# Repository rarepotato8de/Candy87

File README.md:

# Candy87: A universal TKL PCB 💙
The Candy87 Hotswap PCB was exclusively made for and in cooperation with [Candykeys](https://candykeys.com/) and designed to fit the Geonworks F1-8X V2 and other TKL keyboards. It supports many layout options and has awesome features!

## Features
- H87/H88 Compatible
- ISO and/or ANSI Support (See supported layout notes!)
- Standard and Tsangan Bottom Row
- O-Ring Cutouts
- Breakable USB-C Port (Daughterboard can be used with JST)
- Indicator LED's for Caps- and Scrolllock
- RP2040 Chip
- Broken-out GPIO Pins
- QMK/VIAL Support

## Firmware & Flashing
[QMK](https://github.com/qmk/qmk_firmware/tree/master/keyboards/candykeys/candy87) and [VIAL](https://github.com/vial-kb/vial-qmk/tree/vial/keyboards/candykeys/candy87) firmwares are available in their repositories. The compiled VIAL firmware can be found [here](https://github.com/rarepotato8de/Candy87/blob/main/firmware/Candy87_DEFAULT.uf2).

To flash the PCB the first time, you just have to plug it into your computer via. USB-C or Daughterboard and then in your explorer there should appear a new drive medium called "RPI-RP2" or similar. Just drag&drop the .UF2 file onto the drive and the window should automatically close and the PCB will now be flashed and functional.
For flashing it another time, plug in the PCB and hold down the "BOOT" button on the backside of the PCB, press the "RESET" button two times and then release the "BOOT" button again. After that the "RPI-RP2" medium should appear.

## Supported layouts

> [!IMPORTANT]
> Due to hotswap sockets interfering with both ANSI and ISO support, only one of these options can be used at a time.
> Candykeys version comes with ISO by default, but by resoldering two hotswap sockets it can be ANSI. See picture below (it's resoldered to ANSI)

## Breakable USB-C Port
> [!CAUTION]
> Be careful when removing/ breaking-off the USB-C port. It should be done with caution and pliers.
> It's recommended to place the PCB on a flat surface (e.g. a table), with the USB-C port "hanging" off the side and then wiggling up and down with your pliers until it breaks off.

> [!CAUTION]
> Please do this step outside or somewhere but inside.
> You should wear glasses and a mask to prevent any health risks from the FR4 dust.

https://github.com/user-attachments/assets/5fa9985e-4570-457c-9966-bd2f55c6e134

## Open Source

Candy87 was only possible thanks to other open-source projects and libraries (see [Credits](#credits)), so it's open source as well!
You can even order the PCB yourself with the provided files for JLCPCB, and it's pretty affordable :)

## Credits

This project would not exist without these open-source libraries and projects. Massive thanks to all of them!

| Library | Author | Source |
|---|---|---|
| marbastlib | ebastler & contributors | [github.com/ebastler/marbastlib](https://github.com/ebastler/marbastlib) |
| MX_Alps_Hybrid, MX_Only | ai03 | [github.com/ai03-2725/MX_Alps_Hybrid](https://github.com/ai03-2725/MX_Alps_Hybrid) |
| random-keyboard-parts | ai03 | [github.com/ai03-2725/random-keyboard-parts.pretty](https://github.com/ai03-2725/random-keyboard-parts.pretty) |
| bakeneko-60-pcb-rescue | kkatano | [github.com/kkatano/bakeneko-60](https://github.com/kkatano/bakeneko-60) |
| RP2040 libraries | Raspberry Pi Ltd | [datasheets.raspberrypi.com](https://datasheets.raspberrypi.com/) |

License texts can be found in [`hardware/libs/licenses/`](hardware/libs/licenses/).

## Start of this project
The project came up in the beginning of 2024 when Geonworks announced another groupbuy for his popular keyboard, the F1-8X V2. For european fellas, Candykeys wanted to offer an ISO hotswap PCB. So we talked, made plans and finally built this awesome project together!
There was a lot demand for it, people were interested and excited for it and me too! So I'm super honored to be part of this and will look forward for further projects. The Candy87 is the first project I've ever done in cooperation with a company, so I gave my best at all time. Even though we have had an issue with our first prototype, because of switch interference, the second version not only fixed this issue, but was improved even more. From the beginning it was made to be open source, because both Candykeys and I are a fan of this concept.

Big shoutout and thanks to @zitres 🍋🍋 and @candykeys 💙

## Questions?
Feel free to message me!

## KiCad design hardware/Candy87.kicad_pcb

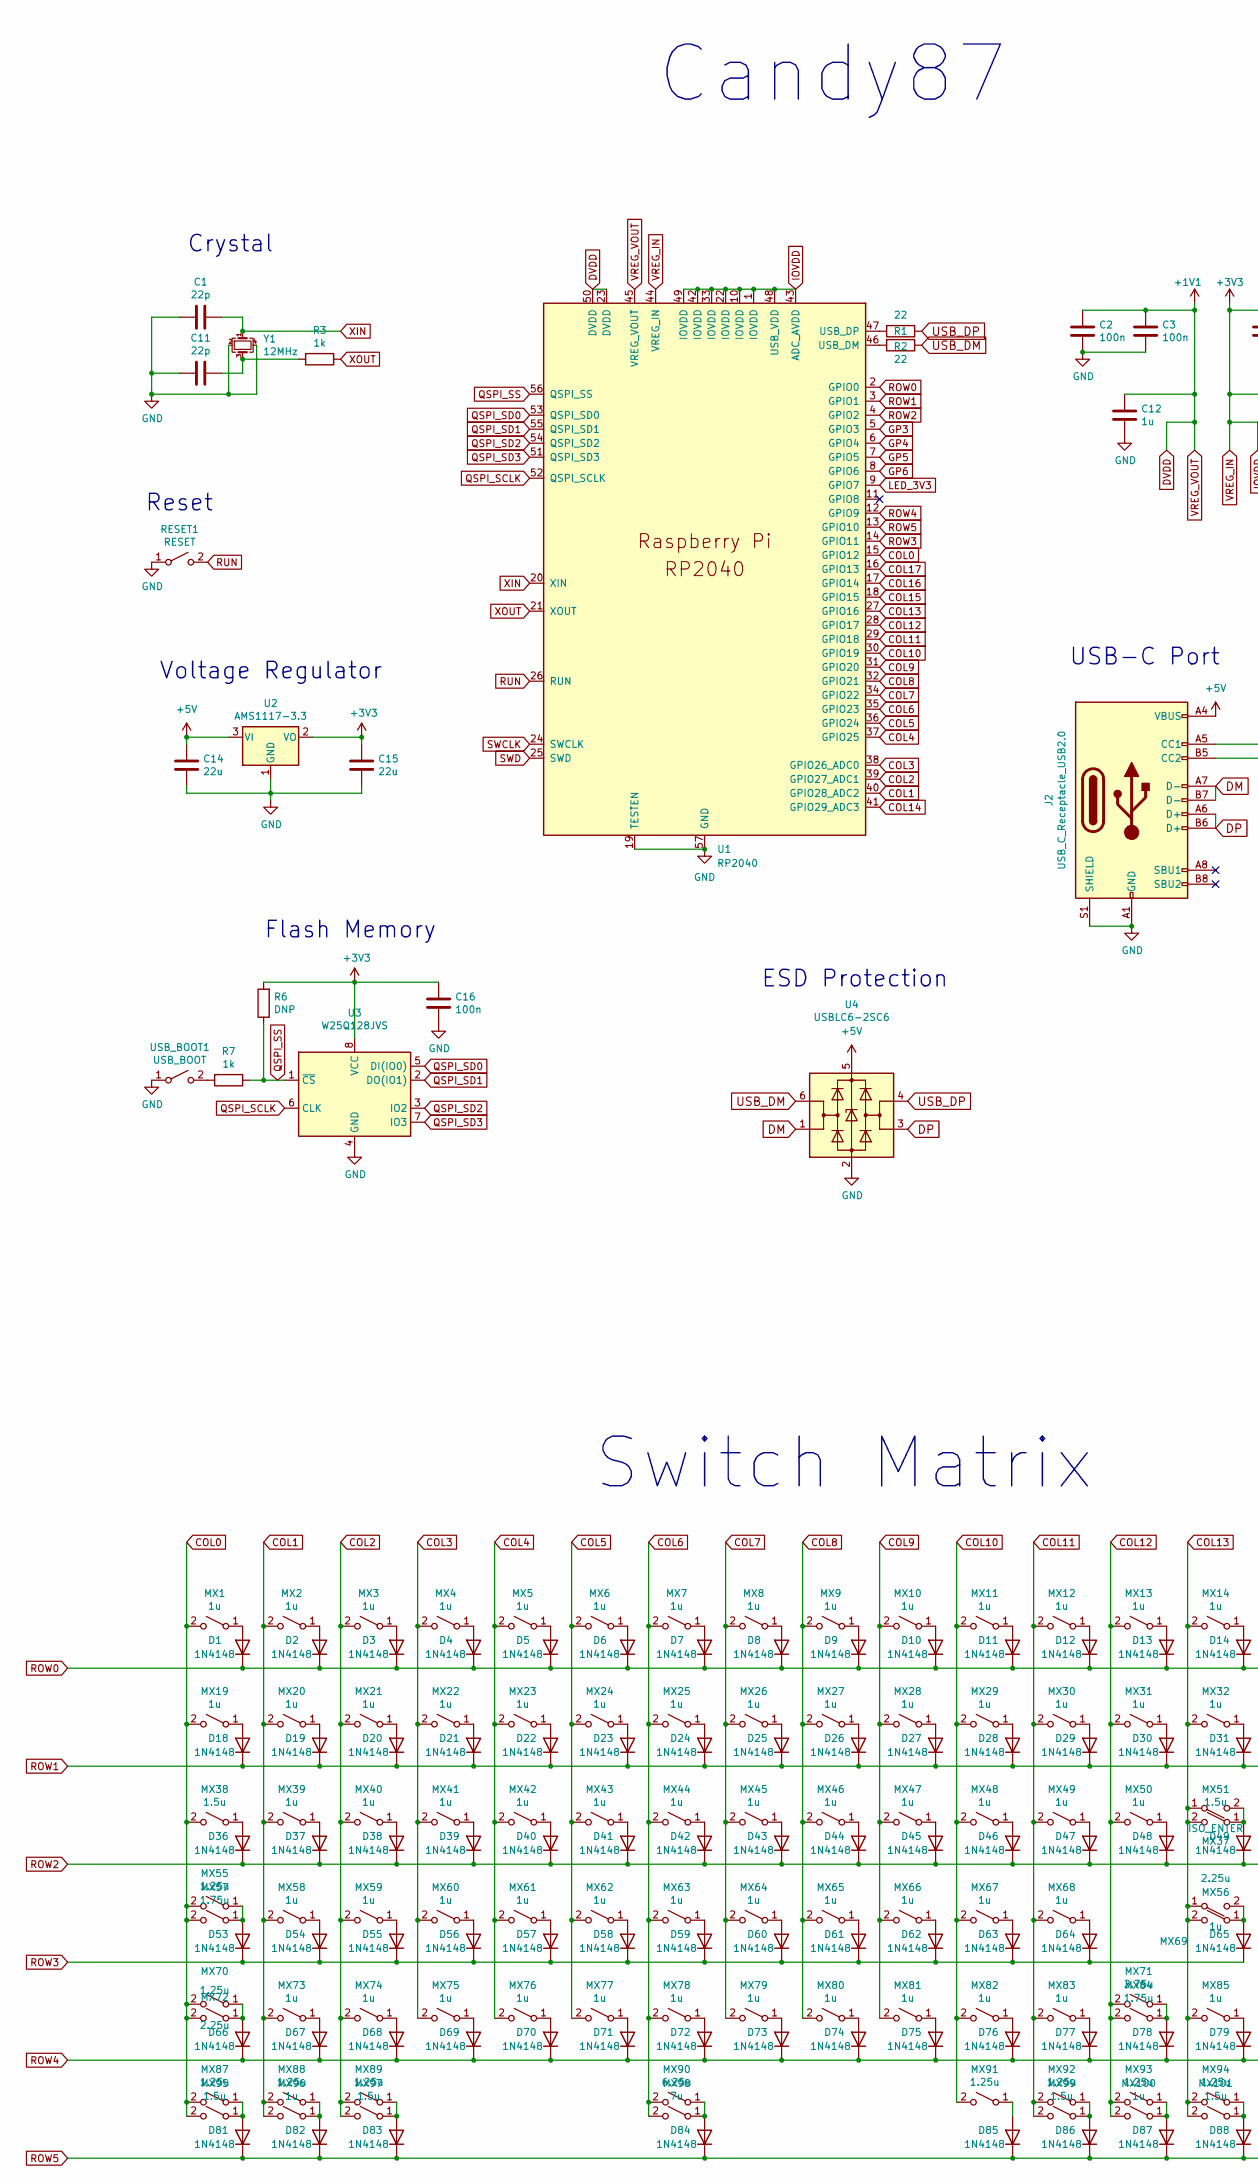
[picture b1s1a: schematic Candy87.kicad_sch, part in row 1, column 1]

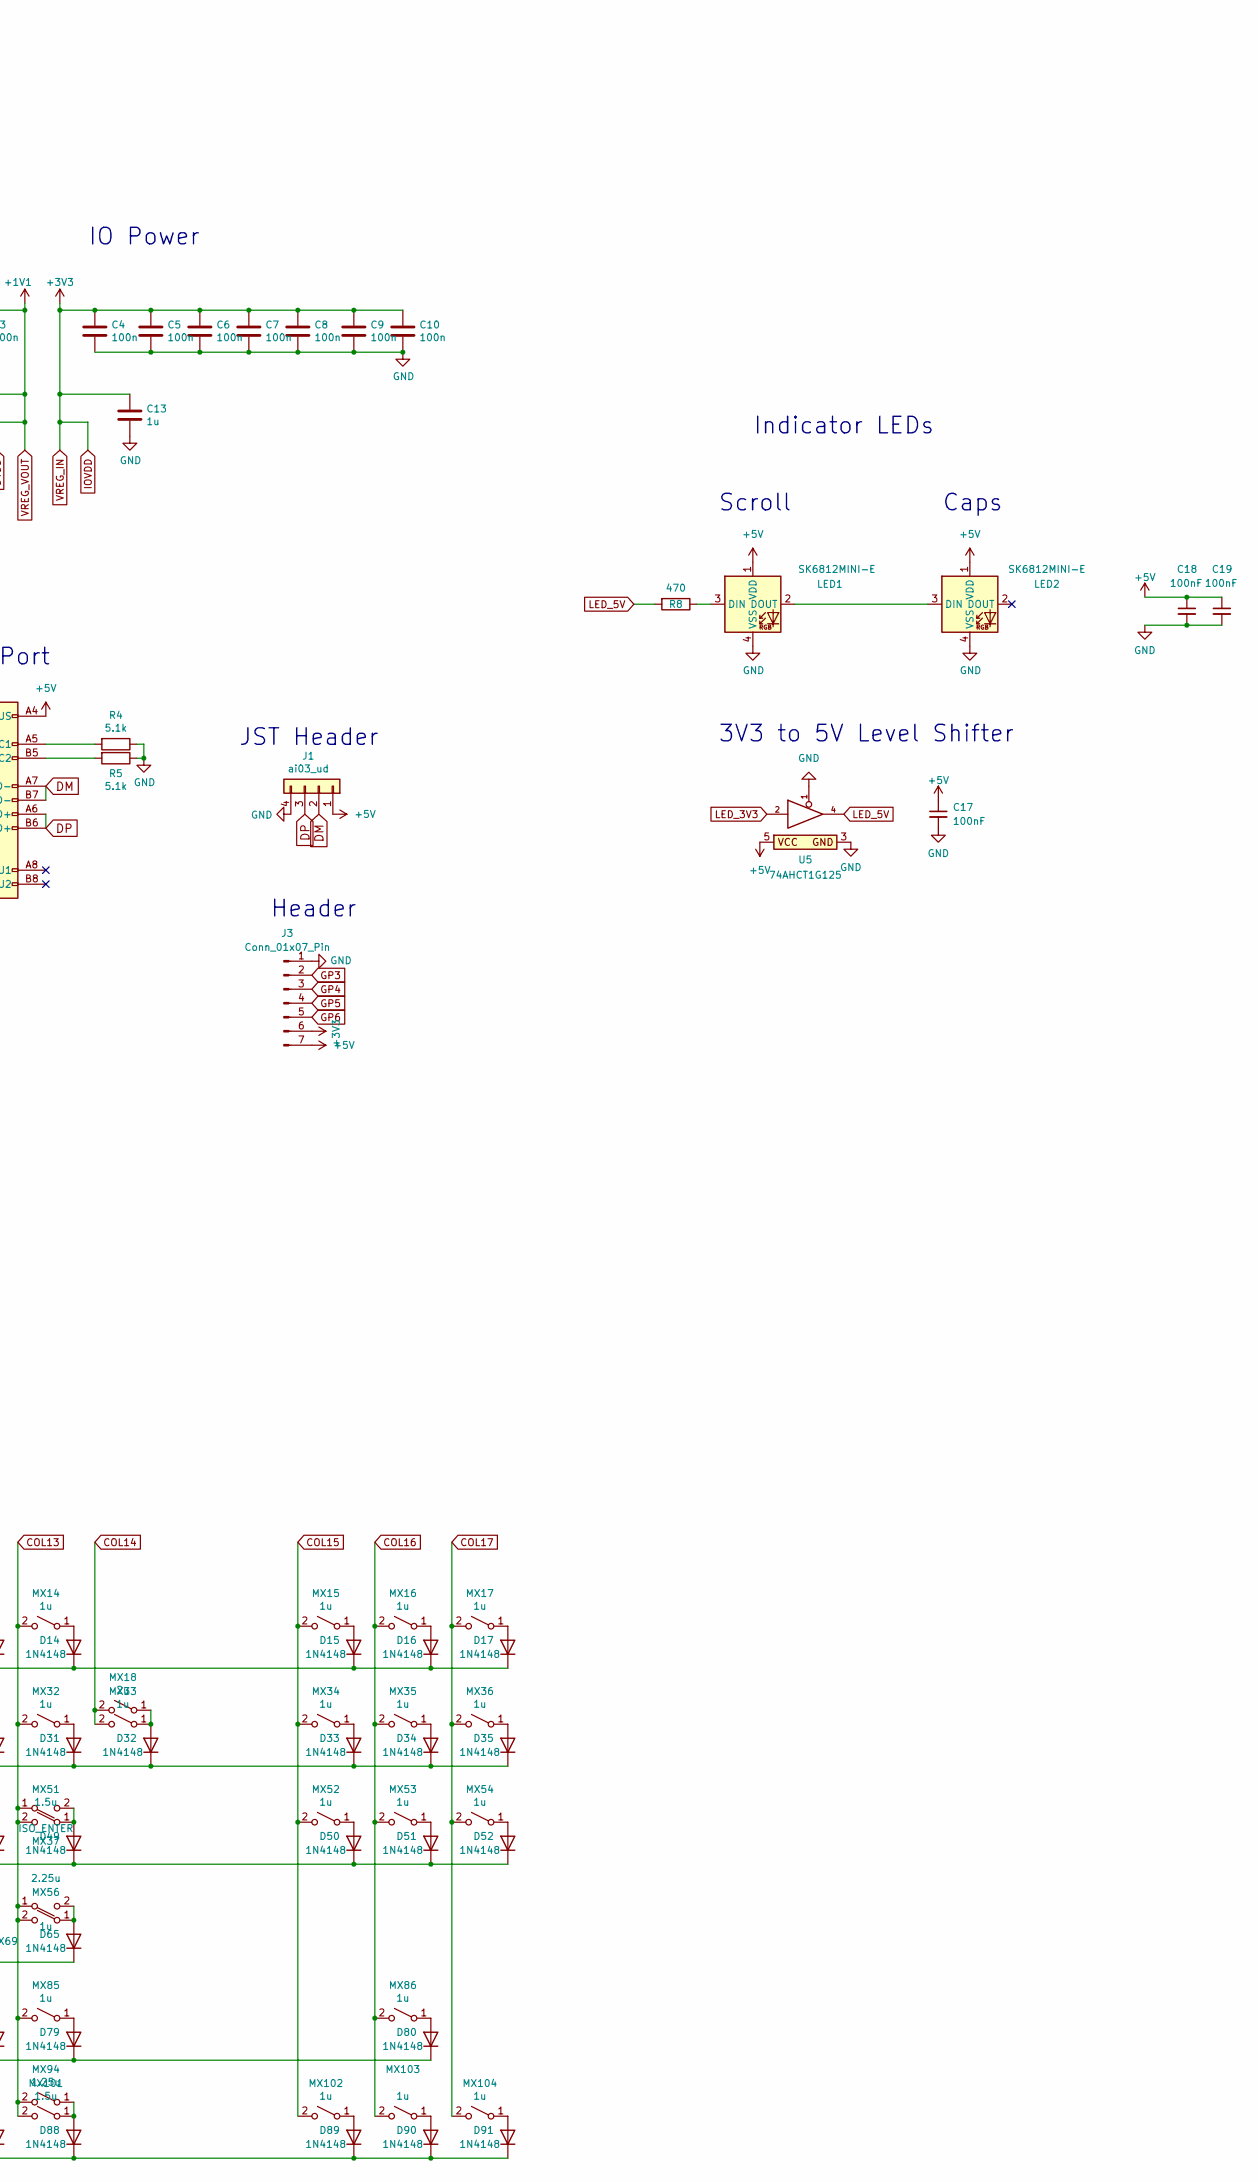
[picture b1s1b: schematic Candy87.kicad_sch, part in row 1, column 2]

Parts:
C1, C11: 22p; C_0603_1608Metric; LCSC C1653
C2, C3, C4, C5, C6, C7, C8, C9, C10, C16: 100n; C_0603_1608Metric; LCSC C14663
C12, C13: 1u; C_0603_1608Metric; LCSC C15849
C14, C15: 22u; C_0603_1608Metric; LCSC C59461
C17, C18, C19: 100nF; C_0402_1005Metric; LCSC C1525
D1, D2, D3, D4, D5, D6, D7, D8, D9, D10, D11, D12, D13, D14, D15, D16, D17, D18, D19, D20, D21, D22, D23, D24, D25, D26, D27, D28, D29, D30, D31, D32, D33, D34, D35, D36, D37, D38, D39, D40, D41, D42, D43, D44, D45, D46, D47, D48, D49, D50, D51, D52, D53, D54, D55, D56, D57, D58, D59, D60, D61, D62, D63, D64, D65, D66, D67, D68, D69, D70, D71, D72, D73, D74, D75, D76, D77, D78, D79, D80, D81, D82, D83, D84, D85, D86, D87, D88, D89, D90, D91: 1N4148; D_SOD-123; LCSC Part # C81598
J1: ai03_ud; JST-SR-4; LCSC C160404
J2: USB_C_Receptacle_USB2.0; USB_C_Receptacle_HRO_TYPE-C-31-M-12; LCSC C165948
J3: Conn_01x07_Pin; PinSocket_1x07_P2.54mm_Vertical
LED1, LED2: SK6812MINI-E; LED_6028R; LCSC C5149201
MX1, MX2, MX3, MX4, MX5, MX6, MX7, MX8, MX9, MX10, MX11, MX12, MX13, MX14, MX15, MX16, MX17, MX19, MX20, MX21, MX22, MX23, MX24, MX25, MX26, MX27, MX28, MX29, MX30, MX31, MX32, MX33, MX34, MX35, MX36, MX39, MX40, MX41, MX42, MX43, MX44, MX45, MX46, MX47, MX48, MX49, MX50, MX52, MX53, MX54, MX56, MX58, MX59, MX60, MX61, MX62, MX63, MX64, MX65, MX66, MX67, MX68, MX73, MX74, MX75, MX76, MX77, MX78, MX79, MX80, MX81, MX82, MX83, MX85, MX86, MX96, MX100, MX102, MX103, MX104: 1u; MXOnly-1U-Hotswap; LCSC C5156480
MX18: 2u; MXOnly-2U-Hotswap; LCSC C5156480
MX37: ISO_ENTER; MXOnly-ISO-Hotswap-ReversedStabilizers; LCSC C5156480
MX38, MX95, MX97, MX99, MX101: 1.5u; MXOnly-1.5U-Hotswap; LCSC C5156480
MX51: 1.5u; MXOnly-1.5U-Hotswap
MX55, MX70, MX87, MX88, MX89, MX91, MX92, MX93, MX94: 1.25u; MXOnly-1.25U-Hotswap; LCSC C5156480
MX57, MX84: 1.75u; MXOnly-1.75U-Hotswap; LCSC C5156480
MX69: 2.25u; MXOnly-2.25U-Hotswap
MX71: 2.75u; MXOnly-2.75U-Hotswap; LCSC C5156480
MX72: 2.25u; MXOnly-2.25U-Hotswap; LCSC C5156480
MX90: 6.25u; MXOnly-6.25U-Hotswap-ReversedStabilizers; LCSC C5156480
MX98: 7u; MXOnly-7U-Hotswap; LCSC C5156480
R1, R2: 22; R_0603_1608Metric; LCSC C23345
R3, R7: 1k; R_0603_1608Metric; LCSC C21190
R4, R5: 5.1k; R_0603_1608Metric; LCSC C23186
R6: DNP; R_0603_1608Metric
R8: 470; R_0603_1608Metric; LCSC C23179
RESET1: RESET; SW_SPST_TL3342; LCSC C318884
U1: RP2040; RP2040-QFN-56; LCSC C2040
U2: AMS1117-3.3; SOT-223-3_TabPin2; LCSC C6186
U3: W25Q128JVS; SOIC-8_5.23x5.23mm_P1.27mm; LCSC C97521
U4: USBLC6-2SC6; SOT-23-6; LCSC C558442
U5: 74AHCT1G125; SOT-23-5; LCSC C7484
USB_BOOT1: USB_BOOT; SW_SPST_TL3342; LCSC C318884
Y1: 12MHz; Crystal_SMD_3225-4Pin_3.2x2.5mm; MPN Crystal MPN; LCSC C518158

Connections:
+5V: C14.1, C17.1, C18.1, C19.1, J1.1, J2.A4 (VBUS), J2.A9 (VBUS), J2.B4 (VBUS), J2.B9 (VBUS), J3.7, LED1.1 (VDD), LED2.1 (VDD), U2.3 (VI), U4.5 (VBUS), U5.5
COL0: MX1.2 (B), MX19.2 (B), MX38.2 (B), MX55.2 (B), MX57.2 (B), MX70.2 (B), MX72.2 (B), MX87.2 (B), MX95.2 (B), U1.15 (GPIO12)
COL1: MX2.2 (B), MX20.2 (B), MX39.2 (B), MX58.2 (B), MX73.2 (B), MX88.2 (B), MX96.2 (B), U1.40 (GPIO28_ADC2); also elsewhere on the board
COL2: MX3.2 (B), MX21.2 (B), MX40.2 (B), MX59.2 (B), MX74.2 (B), MX89.2 (B), MX97.2 (B), U1.39 (GPIO27_ADC1); also elsewhere on the board
COL3: MX4.2 (B), MX22.2 (B), MX41.2 (B), MX60.2 (B), MX75.2 (B), U1.38 (GPIO26_ADC0); also elsewhere on the board
COL4: MX5.2 (B), MX23.2 (B), MX42.2 (B), MX61.2 (B), MX76.2 (B), U1.37 (GPIO25); also elsewhere on the board
COL5: MX6.2 (B), MX24.2 (B), MX43.2 (B), MX62.2 (B), MX77.2 (B), U1.36 (GPIO24)
COL6: MX7.2 (B), MX25.2 (B), MX44.2 (B), MX63.2 (B), MX78.2 (B), MX90.2 (B), MX98.2 (B), U1.35 (GPIO23)
COL7: MX8.2 (B), MX26.2 (B), MX45.2 (B), MX64.2 (B), MX79.2 (B), U1.34 (GPIO22)
COL8: MX9.2 (B), MX27.2 (B), MX46.2 (B), MX65.2 (B), MX80.2 (B), U1.32 (GPIO21)
COL9: MX10.2 (B), MX28.2 (B), MX47.2 (B), MX66.2 (B), MX81.2 (B), U1.31 (GPIO20); also elsewhere on the board
COL10: MX11.2 (B), MX29.2 (B), MX48.2 (B), MX67.2 (B), MX82.2 (B), MX91.2 (B), U1.30 (GPIO19); also elsewhere on the board
COL11: MX12.2 (B), MX30.2 (B), MX49.2 (B), MX68.2 (B), MX83.2 (B), MX92.2 (B), MX99.2 (B), U1.29 (GPIO18); also elsewhere on the board
COL12: MX13.2 (B), MX31.2 (B), MX50.2 (B), MX71.2 (B), MX84.2 (B), MX93.2 (B), MX100.2 (B), U1.28 (GPIO17); also elsewhere on the board
COL13: MX14.2 (B), MX32.2 (B), MX37.1 (A), MX51.2 (B), MX56.1 (A), MX69.2 (B), MX85.2 (B), MX94.2 (B), MX101.2 (B), U1.27 (GPIO16)
COL14: MX18.2 (B), MX33.2 (B), U1.41 (GPIO29_ADC3)
COL15: MX15.2 (B), MX34.2 (B), MX52.2 (B), MX102.2 (B), U1.18 (GPIO15)
COL16: MX16.2 (B), MX35.2 (B), MX53.2 (B), MX86.2 (B), MX103.2 (B), U1.17 (GPIO14)
COL17: MX17.2 (B), MX36.2 (B), MX54.2 (B), MX104.2 (B), U1.16 (GPIO13)
DM: J1.2, J2.A7 (D-), J2.B7 (D-), U4.1 (I/O1)
DP: J1.3, J2.A6 (D+), J2.B6 (D+), U4.3 (I/O2)
DVDD: C2.1, C3.1, C12.1, U1.23 (DVDD), U1.45 (VREG_VOUT), U1.50 (DVDD)
GND: C1.2, C2.2, C3.2, C4.2, C5.2, C6.2, C7.2, C8.2, C9.2, C10.2, C11.2, C12.2, C13.2, C14.2, C15.2, C16.2, C17.2, C18.2, C19.2, J1.4, J2.A1 (GND), J2.A12 (GND), J2.B1 (GND), J2.B12 (GND), J2.S1 (SHIELD), J3.1, LED1.4 (VSS), LED2.4 (VSS), R4.1, R5.1, RESET1.1 (A), U1.19 (TESTEN), U1.57 (GND), U2.1 (GND), U3.4 (GND), U4.2 (GND), U5.1, U5.3, USB_BOOT1.1 (A), Y1.2, Y1.4
GP3: J3.2, U1.5 (GPIO3)
GP4: J3.3, U1.6 (GPIO4)
GP5: J3.4, U1.7 (GPIO5)
GP6: J3.5, U1.8 (GPIO6)
IOVDD: C4.1, C5.1, C6.1, C7.1, C8.1, C9.1, C10.1, C13.1, C15.1, C16.1, J3.6, R6.2, U1.1 (IOVDD), U1.10 (IOVDD), U1.22 (IOVDD), U1.33 (IOVDD), U1.42 (IOVDD), U1.43 (ADC_AVDD), U1.44 (VREG_IN), U1.48 (USB_VDD), U1.49 (IOVDD), U2.2 (VO), U3.8 (VCC)
LED_3V3: U1.9 (GPIO7), U5.2
LED_5V: R8.2, U5.4
unnamed: C11.1, R3.2, Y1.3
unnamed: D1.2 (A), MX1.1 (A)
unnamed 32: D2.2 (A), MX2.1 (A); also elsewhere on the board
unnamed 33: D3.2 (A), MX3.1 (A); also elsewhere on the board
unnamed 34: D4.2 (A), MX4.1 (A); also elsewhere on the board
unnamed 35: D5.2 (A), MX5.1 (A); also elsewhere on the board
unnamed: D6.2 (A), MX6.1 (A)
unnamed: D7.2 (A), MX7.1 (A)
unnamed: D8.2 (A), MX8.1 (A)
unnamed: D9.2 (A), MX9.1 (A)
unnamed 40: D10.2 (A), MX10.1 (A); also elsewhere on the board
unnamed 41: D11.2 (A), MX11.1 (A); also elsewhere on the board
unnamed 42: D12.2 (A), MX12.1 (A); also elsewhere on the board
unnamed 43: D13.2 (A), MX13.1 (A); also elsewhere on the board
unnamed: D14.2 (A), MX14.1 (A)
unnamed: D15.2 (A), MX15.1 (A)
unnamed: D16.2 (A), MX16.1 (A)
unnamed: D17.2 (A), MX17.1 (A)
unnamed: D18.2 (A), MX19.1 (A)
unnamed: D19.2 (A), MX20.1 (A)
unnamed: D20.2 (A), MX21.1 (A)
unnamed: D21.2 (A), MX22.1 (A)
unnamed: D22.2 (A), MX23.1 (A)
unnamed: D23.2 (A), MX24.1 (A)
unnamed: D24.2 (A), MX25.1 (A)
unnamed: D25.2 (A), MX26.1 (A)
unnamed: D26.2 (A), MX27.1 (A)
unnamed: D27.2 (A), MX28.1 (A)
unnamed: D28.2 (A), MX29.1 (A)
unnamed: D29.2 (A), MX30.1 (A)
unnamed: D30.2 (A), MX31.1 (A)
unnamed: D31.2 (A), MX32.1 (A)
unnamed: D32.2 (A), MX18.1 (A), MX33.1 (A)
unnamed: D33.2 (A), MX34.1 (A)
unnamed: D34.2 (A), MX35.1 (A)
unnamed: D35.2 (A), MX36.1 (A)
unnamed: D36.2 (A), MX38.1 (A)
unnamed: D37.2 (A), MX39.1 (A)
unnamed: D38.2 (A), MX40.1 (A)
unnamed: D39.2 (A), MX41.1 (A)
unnamed: D40.2 (A), MX42.1 (A)
unnamed: D41.2 (A), MX43.1 (A)
unnamed: D42.2 (A), MX44.1 (A)
unnamed: D43.2 (A), MX45.1 (A)
unnamed: D44.2 (A), MX46.1 (A)
unnamed: D45.2 (A), MX47.1 (A)
unnamed: D46.2 (A), MX48.1 (A)
unnamed: D47.2 (A), MX49.1 (A)
unnamed: D48.2 (A), MX50.1 (A)
unnamed: D49.2 (A), MX37.2 (B), MX51.1 (A)
unnamed: D50.2 (A), MX52.1 (A)
unnamed: D51.2 (A), MX53.1 (A)
unnamed: D52.2 (A), MX54.1 (A)
unnamed: D53.2 (A), MX55.1 (A), MX57.1 (A)
unnamed: D54.2 (A), MX58.1 (A)
unnamed: D55.2 (A), MX59.1 (A)
unnamed: D56.2 (A), MX60.1 (A)
unnamed: D57.2 (A), MX61.1 (A)
unnamed: D58.2 (A), MX62.1 (A)
unnamed: D59.2 (A), MX63.1 (A)
unnamed: D60.2 (A), MX64.1 (A)
unnamed: D61.2 (A), MX65.1 (A)
unnamed: D62.2 (A), MX66.1 (A)
unnamed: D63.2 (A), MX67.1 (A)
unnamed: D64.2 (A), MX68.1 (A)
unnamed: D65.2 (A), MX56.2 (B), MX69.1 (A)
unnamed: D66.2 (A), MX70.1 (A), MX72.1 (A)
unnamed: D67.2 (A), MX73.1 (A)
unnamed: D68.2 (A), MX74.1 (A)
unnamed: D69.2 (A), MX75.1 (A)
unnamed: D70.2 (A), MX76.1 (A)
unnamed: D71.2 (A), MX77.1 (A)
unnamed: D72.2 (A), MX78.1 (A)
unnamed: D73.2 (A), MX79.1 (A)
unnamed: D74.2 (A), MX80.1 (A)
unnamed: D75.2 (A), MX81.1 (A)
unnamed: D76.2 (A), MX82.1 (A)
unnamed: D77.2 (A), MX83.1 (A)
unnamed: D78.2 (A), MX71.1 (A), MX84.1 (A)
unnamed: D79.2 (A), MX85.1 (A)
unnamed: D80.2 (A), MX86.1 (A)
unnamed: D81.2 (A), MX87.1 (A), MX95.1 (A)
unnamed: D82.2 (A), MX88.1 (A), MX96.1 (A)
unnamed: D83.2 (A), MX89.1 (A), MX97.1 (A)
unnamed: D84.2 (A), MX90.1 (A), MX98.1 (A)
unnamed: D85.2 (A), MX91.1 (A)
unnamed: D86.2 (A), MX92.1 (A), MX99.1 (A)
unnamed: D87.2 (A), MX93.1 (A), MX100.1 (A)
unnamed: D88.2 (A), MX94.1 (A), MX101.1 (A)
unnamed: D89.2 (A), MX102.1 (A)
unnamed: D90.2 (A), MX103.1 (A)
unnamed: D91.2 (A), MX104.1 (A)
unnamed: J2.A5 (CC1), R4.2
unnamed: J2.B5 (CC2), R5.2
unnamed: LED1.3 (DIN), R8.1
unnamed: LED1.2 (DOUT), LED2.3 (DIN)
unnamed: R2.2, U1.46 (USB_DM)
unnamed: R1.2, U1.47 (USB_DP)
unnamed: R7.2, USB_BOOT1.2 (B)
QSPI_SCLK: U1.52 (QSPI_SCLK), U3.6 (CLK)
QSPI_SD0: U1.53 (QSPI_SD0), U3.5 (DI(IO0))
QSPI_SD1: U1.55 (QSPI_SD1), U3.2 (DO(IO1))
QSPI_SD2: U1.54 (QSPI_SD2), U3.3 (IO2)
QSPI_SD3: U1.51 (QSPI_SD3), U3.7 (IO3)
QSPI_SS: R6.1, R7.1, U1.56 (QSPI_SS), U3.1 (~CS)
ROW0: D1.1 (K), D2.1 (K), D3.1 (K), D4.1 (K), D5.1 (K), D6.1 (K), D7.1 (K), D8.1 (K), D9.1 (K), D10.1 (K), D11.1 (K), D12.1 (K), D13.1 (K), D14.1 (K), D15.1 (K), D16.1 (K), D17.1 (K), U1.2 (GPIO0)
ROW1: D18.1 (K), D19.1 (K), D20.1 (K), D21.1 (K), D22.1 (K), D23.1 (K), D24.1 (K), D25.1 (K), D26.1 (K), D27.1 (K), D28.1 (K), D29.1 (K), D30.1 (K), D31.1 (K), D32.1 (K), D33.1 (K), D34.1 (K), D35.1 (K), U1.3 (GPIO1)
ROW2: D36.1 (K), D37.1 (K), D38.1 (K), D39.1 (K), D40.1 (K), D41.1 (K), D42.1 (K), D43.1 (K), D44.1 (K), D45.1 (K), D46.1 (K), D47.1 (K), D48.1 (K), D49.1 (K), D50.1 (K), D51.1 (K), D52.1 (K), U1.4 (GPIO2)
ROW3: D53.1 (K), D54.1 (K), D55.1 (K), D56.1 (K), D57.1 (K), D58.1 (K), D59.1 (K), D60.1 (K), D61.1 (K), D62.1 (K), D63.1 (K), D64.1 (K), D65.1 (K), U1.14 (GPIO11)
ROW4: D66.1 (K), D67.1 (K), D68.1 (K), D69.1 (K), D70.1 (K), D71.1 (K), D72.1 (K), D73.1 (K), D74.1 (K), D75.1 (K), D76.1 (K), D77.1 (K), D78.1 (K), D79.1 (K), D80.1 (K), U1.12 (GPIO9)
ROW5: D81.1 (K), D82.1 (K), D83.1 (K), D84.1 (K), D85.1 (K), D86.1 (K), D87.1 (K), D88.1 (K), D89.1 (K), D90.1 (K), D91.1 (K), U1.13 (GPIO10)
RUN: RESET1.2 (B), U1.26 (RUN)
SWCLK: U1.24 (SWCLK)
SWD: U1.25 (SWD)
USB_DM: R2.1, U4.6 (I/O1)
USB_DP: R1.1, U4.4 (I/O2)
XIN: C1.1, U1.20 (XIN), Y1.1
XOUT: R3.1, U1.21 (XOUT)

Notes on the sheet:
Crystal
Header
IO Power
Caps
Flash Memory
Scroll
3V3 to 5V Level Shifter
Candy87
Voltage Regulator
Reset
JST Header
Indicator LEDs
USB-C Port
ESD Protection
Switch Matrix

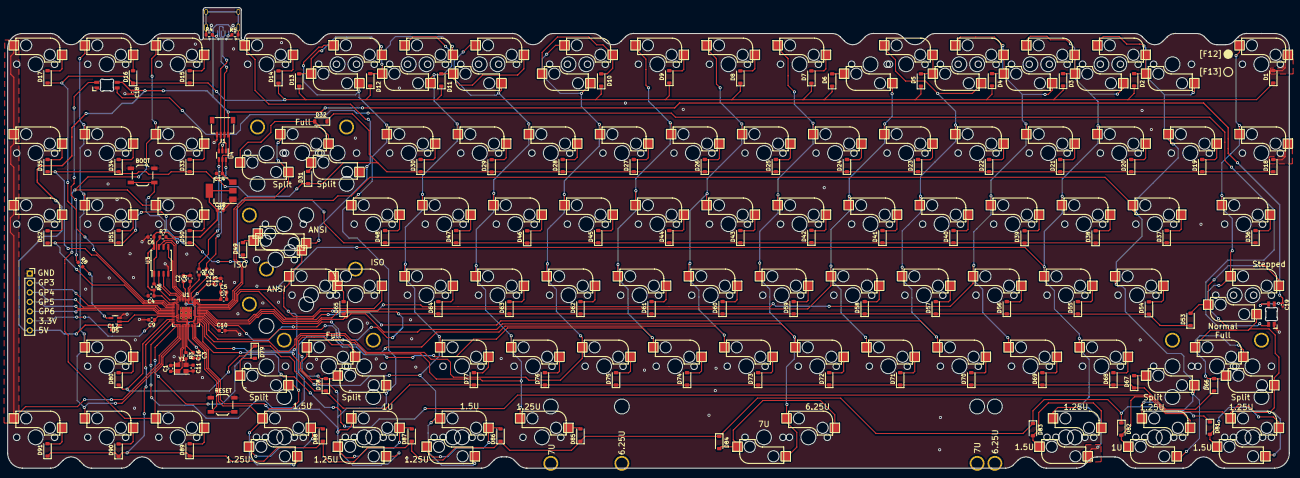
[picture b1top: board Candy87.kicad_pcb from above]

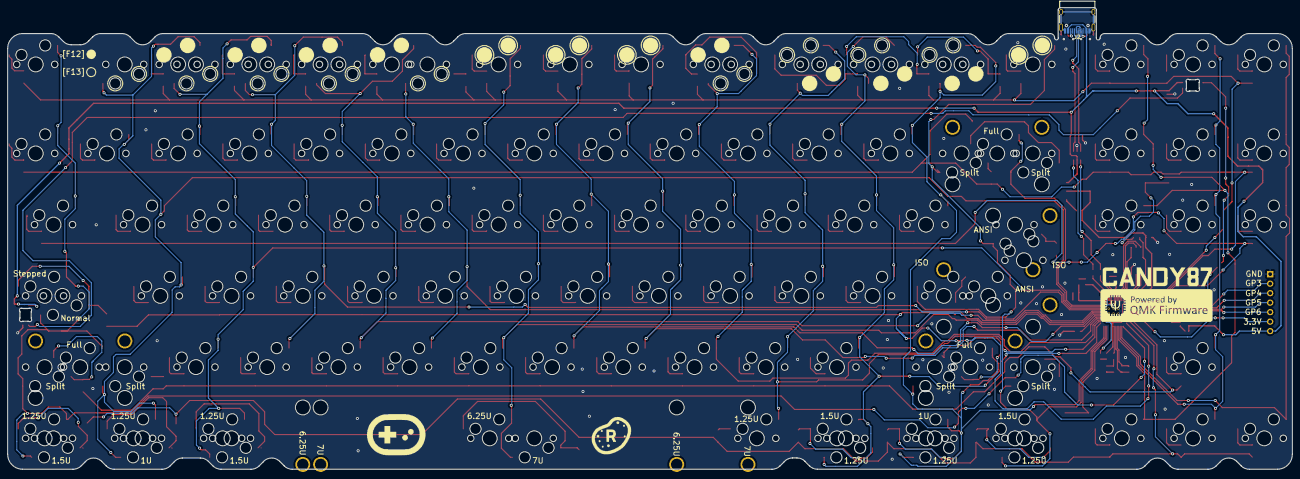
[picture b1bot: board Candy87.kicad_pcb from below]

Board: 2 copper layers, 343.6 x 123.5 mm, 245 parts (115 on the bottom side), 146 nets.

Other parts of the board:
MX2#2, MX3#2, MX4#2, MX5#2, MX10#2, MX11#2, MX12#2, MX13#2: 1u; MXOnly-1U-Hotswap
Ref**: Val**; candy87-5
Ref**#2: Val**; rarepotato

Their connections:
COL1: MX2#2.2 (B); also elsewhere on the board
COL2: MX3#2.2 (B); also elsewhere on the board
COL3: MX4#2.2 (B); also elsewhere on the board
COL4: MX5#2.2 (B); also elsewhere on the board
COL9: MX10#2.2 (B); also elsewhere on the board
COL10: MX11#2.2 (B); also elsewhere on the board
COL11: MX12#2.2 (B); also elsewhere on the board
COL12: MX13#2.2 (B); also elsewhere on the board
unnamed 32: MX2#2.1 (A); also elsewhere on the board
unnamed 33: MX3#2.1 (A); also elsewhere on the board
unnamed 34: MX4#2.1 (A); also elsewhere on the board
unnamed 35: MX5#2.1 (A); also elsewhere on the board
unnamed 40: MX10#2.1 (A); also elsewhere on the board
unnamed 41: MX11#2.1 (A); also elsewhere on the board
unnamed 42: MX12#2.1 (A); also elsewhere on the board
unnamed 43: MX13#2.1 (A); also elsewhere on the board

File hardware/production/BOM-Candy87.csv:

Comment,Designator,Footprint,LCSC
100n,"C10,C16,C2,C3,C4,C5,C6,C7,C8,C9",C_0603_1608Metric,C14663
100nF,"C17,C18,C19",C_0402_1005Metric,C1525
1u,"C12,C13",C_0603_1608Metric,C15849
ai03_ud,J1,JST-SR-4,C160404
22p,"C1,C11",C_0603_1608Metric,C1653
USB_C_Receptacle_USB2.0,J2,USB_C_Receptacle_HRO_TYPE-C-31-M-12,C165948
RP2040,U1,RP2040-QFN-56,C2040
1k,"R3,R7",R_0603_1608Metric,C21190
470,R8,R_0603_1608Metric,C23179
5.1k,"R4,R5",R_0603_1608Metric,C23186
22,"R1,R2",R_0603_1608Metric,C23345
RESET,"RESET1,USB_BOOT1",SW_SPST_TL3342,C318884
SK6812MINI-E,"LED1,LED2",LED_6028R,C5149201
1u,"MX1,MX10,MX100,MX101,MX102,MX103,MX104,MX11,MX12,MX13,MX14,MX15,MX16,MX17,MX18,MX19,MX2,MX20,MX21,MX22,MX23,MX24,MX25,MX26,MX27,MX28,MX29,MX3,MX30,MX31,MX32,MX33,MX34,MX35,MX36,MX37,MX38,MX39,MX4,MX40,MX41,MX42,MX43,MX44,MX45,MX46,MX47,MX48,MX49,MX5,MX50,MX52,MX53,MX54,MX55,MX56,MX57,MX58,MX59,MX6,MX60,MX61,MX62,MX63,MX64,MX65,MX66,MX67,MX68,MX7,MX70,MX71,MX72,MX73,MX74,MX75,MX76,MX77,MX78,MX79,MX8,MX80,MX81,MX82,MX83,MX84,MX85,MX86,MX87,MX88,MX89,MX9,MX90,MX91,MX92,MX93,MX94,MX95,MX96,MX97,MX98,MX99",MXOnly-1U-Hotswap,C5156480
12MHz,Y1,Crystal_SMD_3225-4Pin_3.2x2.5mm,C518158
USBLC6-2SC6,U4,SOT-23-6,C558442
22u,"C14,C15",C_0603_1608Metric,C59461
AMS1117-3.3,U2,SOT-223-3_TabPin2,C6186
74AHCT1G125,U5,SOT-23-5,C7484
1N4148,"D1,D10,D11,D12,D13,D14,D15,D16,D17,D18,D19,D2,D20,D21,D22,D23,D24,D25,D26,D27,D28,D29,D3,D30,D31,D32,D33,D34,D35,D36,D37,D38,D39,D4,D40,D41,D42,D43,D44,D45,D46,D47,D48,D49,D5,D50,D51,D52,D53,D54,D55,D56,D57,D58,D59,D6,D60,D61,D62,D63,D64,D65,D66,D67,D68,D69,D7,D70,D71,D72,D73,D74,D75,D76,D77,D78,D79,D8,D80,D81,D82,D83,D84,D85,D86,D87,D88,D89,D9,D90,D91",D_SOD-123,C81598
W25Q128JVS,U3,SOIC-8_5.23x5.23mm_P1.27mm,C97521

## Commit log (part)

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2026-03-21 OPEN SOURCE!
    Lets go, finally made it open source! Thanks to Candykeys (now called InputGear) for allowing me.
